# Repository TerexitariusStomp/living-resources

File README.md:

# living-resources

A living sensing commons: cheap, passive, **universal** field nodes relay
multimodal ecological detections over Reticulum to a Playnet edge, where
readings become witnessed receipts and receipts become credit for the
ecology that produced them.

License: AGPL-3.0-or-later.

## The node

One board, every lane's electronics populated (~$35–45 BOM):

camera (OV2640) · air mic (INMP441, 48 kHz/16-bit) · env
(BME280/BH1750/PIR) · hydrophone front-end · ultrasonic MEMS (20–100 kHz)
· C4D contactless front-end · 40 kHz emit transducer · microSD · Reticulum
(WiFi/LoRa/satellite)

A node's role is software + which head is in the environment — never a
different product. See `spec/living-resources.md`.

## The rules that make it a commons

- Every ecological subject is an agent with a human guardian and
  **voice 0** — it earns, it never speaks.
- `sense`/`fleet` lanes admit on **evidence** (a SAID on the lane's gate).
- `emit`/`cast`/`store` admit on **joint guardian+operator consent** —
  bio-write and cloud-write are decisions, not defaults.
- `hop`/`compute`/`engineered` refuse outright — consent is not evidence.
- Every refusal is a structured value; every emission is logged and
  receipted.

## Quickstart

```bash
make test                  # e2e under guile; static checks without it
make check-custom-budget   # the ≤5% first-party rule
```

E0 field validation (see `docs/EXPERIMENTS.md`): flash
`firmware/node/main.py` to a XIAO ESP32-S3 Sense, run the edge adapters
against the node's detection stream, score detections blinded.

## Layout

```
module/living/   specs · agents · sense-subject · attest · settlement · offers
adapters/        mic · camera · reticulum · weather   (thin seams; ML stays
                 Python-side)
firmware/node/   MicroPython universal node (incl. consent-gated EmitLane)
deploy/policies/ OPA: lane-gate.rego · consent.rego
spec/            the system spec
docs/            ARCHITECTURE (component map) · SCIENCE (claim table)
                 · EXPERIMENTS (E-gates) · ROADMAP · CONNECTOME
                 · EFFICIENCY · FUNDING (+ funding/ app drafts)
tests/e2e/       sensing-cell · refused-lanes · write-lanes
tools/edge/      classify.py (edge ML seam) · rns_edge.py (LXMF daemon)
tools/e0/        score.py (blinded field-validation scorer)
tools/e5/        relay_check.py (E5 hop-graduation harness)
```

## Non-interference

Passive by default: nothing attaches to an organism, nothing enters soil,
no anchor moorings, no flash or IR. Emission exists — it is a lane the
commons can ride — and it rides only on recorded joint consent, at
duty-cycled minimum power, with every burst on the ledger.

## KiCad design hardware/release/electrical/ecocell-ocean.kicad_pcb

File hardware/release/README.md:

# EcoCell Ocean — Engineering Release

This directory is the manufacturing package for the ocean-capable EcoCell
node: pressure-rated submerged electronics body plus a minimal-signature
tether float (GPS, antenna, solar). One serialized design covers both the
tether-float and fully submerged-pod forms — the same node electronics,
deployment role chosen by firmware flags.

## Release levels

- **R0 — prototype fab package.** A supplier-reviewable package a fab can
  quote and build from: native KiCad sources, netlist, DSN, Gerbers +
  drill, CPL, controlled BOM, assembly + harness drawings, stack-up/fab
  drawing, test plan, unit traveler, and this README with a checksummed
  manifest. R0 does **not** claim validated pressure rating, ecological
  benefit, or field performance — it claims the design files are
  consistent, DRC-clean, and buildable.
- **R1 — validated build.** R0 plus: assembled units pass TEST-PLAN,
  pressure/leak spec verified on the hull, Salton Sea serialized trial
  complete, DFM/DFT review closed with the supplier.

## Configuration identity

| Item | Value |
|---|---|
| Board | `ecocell-ocean` — 120 × 90 mm, 4-layer (F.Cu / In1 GND / In2 +3V3 / B.Cu) |
| Electrical rev | generated by `tools/pcb/gen_ocean_sch.py` + `gen_ocean_pcb.py` from the same netlist |
| Enclosure revision | `TBD` — pressure-hull + biota-disguised float CAD pending |
| Firmware revision | `firmware/node/main.py` as committed; image hash recorded per unit |
| Regional radio variant | `E22-400M22S` (433 MHz) or `E22-900M22S` (868/915) — one per build, declared |
| Approved suppliers | `TBD` — quote-backed, per-part, with lifecycle/stock check |

## Regenerating the electrical package

```
python3 tools/pcb/gen_ocean_sch.py          # writes electrical/ecocell-ocean.net
python3 tools/pcb/gen_ocean_pcb.py          # placement + DSN export
STITCH=1 python3 tools/pcb/gen_ocean_pcb.py # adds the stitch router (slow)
POST_ONLY=1 python3 tools/pcb/gen_ocean_pcb.py
    # resume: re-run only the post-attach island pass on the saved board
```

Fabrication rules baked into the generator: ≥0.2 mm clearance, ≥0.15 mm
track, 0.5/0.3 mm vias, ≥0.5 mm copper-to-edge, mounting-hole and
ESP32 antenna keepouts.

Known substitutions vs the ideal BOM:

| Ref | Part | Footprint used | Note |
|---|---|---|---|
| U_CHG | TP4056 | `SOIC-8-1EP_3.9x4.9mm_P1.27mm_EP2.41x3.81mm` | ESOP-8 footprint absent from stock KiCad libs; pin-compatible SOIC-8-EP used — verify land pattern against the chosen charger MPN before ordering |

## Release artifacts (required for R0)

| Artifact | Path / source | Status |
|---|---|---|
| Native KiCad schematic | `hardware/release/electrical/ecocell-ocean.net` | **present** — deterministic netlist emitter (SKiDL source lost in workspace wipe; regenerate `.kicad_sch` pending) |
| Native KiCad PCB | `hardware/release/electrical/ecocell-ocean.kicad_pcb` | **present** — placed + autorouted; DRC status tracked below |
| Gerbers + drill (or IPC-2581) | `hardware/release/electrical/` | **missing** — export after DRC is clean |
| Board stack-up / fab drawing | `hardware/release/FAB-NOTES.md` | **present** — stack-up + CAM notes; fiducials flagged as R0 gap |
| Controlled BOM (MPN + alternates) | `hardware/release/electrical/ecocell-ocean-bom.csv` | **present** — generated from the netlist; MPNs/quoting unverified |
| CPL with verified origin/rotation | `hardware/release/assembly/` | **missing** — export post-DRC |
| Assembly drawing | `hardware/release/assembly/` | **missing** |
| Harness drawings | `hardware/release/HARNESS.md` | **present** — connector pinouts + tether spec from the netlist |
| Mechanical CAD + STEP + drawings | `hardware/release/mechanical/` | **missing** — pressure hull, optical port, tether, float |
| Pressure/leak spec | `hardware/release/PRESSURE-SPEC.md` | **present** — 0.4 MPa working / 0.6 MPa proof envelope; hull FEA + O-ring sizing open |
| Test fixture spec | `hardware/release/TEST-PLAN.md` | **present** |
| Unit traveler / calibration record | `hardware/release/UNIT-TRAVELER.md` | **present** |
| Firmware image + hash | `hardware/release/firmware-image.json` | **partial** — source-tree hash recorded; reproducible cross-build pending |
| Release manifest + checksums | `hardware/release/manifest.json` | **present** |
| DFM/DFT review record | `hardware/release/` | **missing** — supplier engagement required |

No artifact may be silently replaced: any change goes through the ECO
procedure below and bumps the relevant revision.

## ECO procedure

1. Describe the change in `CHANGELOG.md` (rev, scope, reason, risk).
2. Regenerate affected artifacts from source — never hand-edit Gerbers,
   CPL, or the manifest.
3. Re-run DRC on the board and the repo checks (`make test`,
   `make check-custom-budget`); record results in the manifest.
4. Re-hash every shipped artifact into `manifest.json` and bump the
   package checksum.
5. A second reviewer signs off before the package is quoted to a fab.

## Honest-status notes

- The board currently validates as *routed*, not *fabrication-ready*:
  DRC must report 0 errors/0 unconnected before Gerbers are exported
  and the "KiCad PCB" row moves to verified.
- Acoustic playback hardware (emit lane) is consent-gated in firmware
  and policy; no ecological effect is claimed from this package.

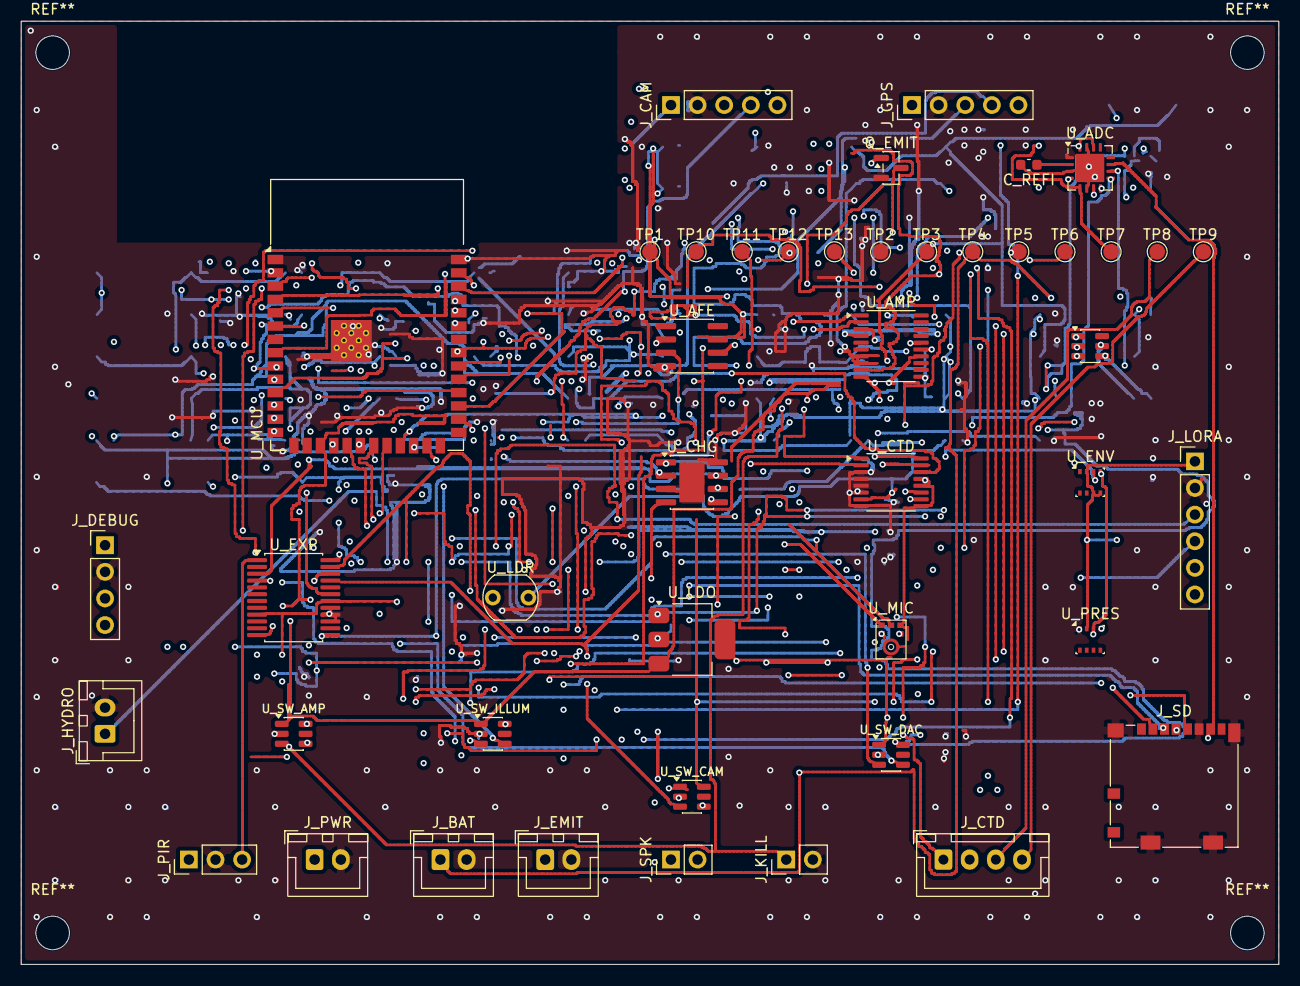
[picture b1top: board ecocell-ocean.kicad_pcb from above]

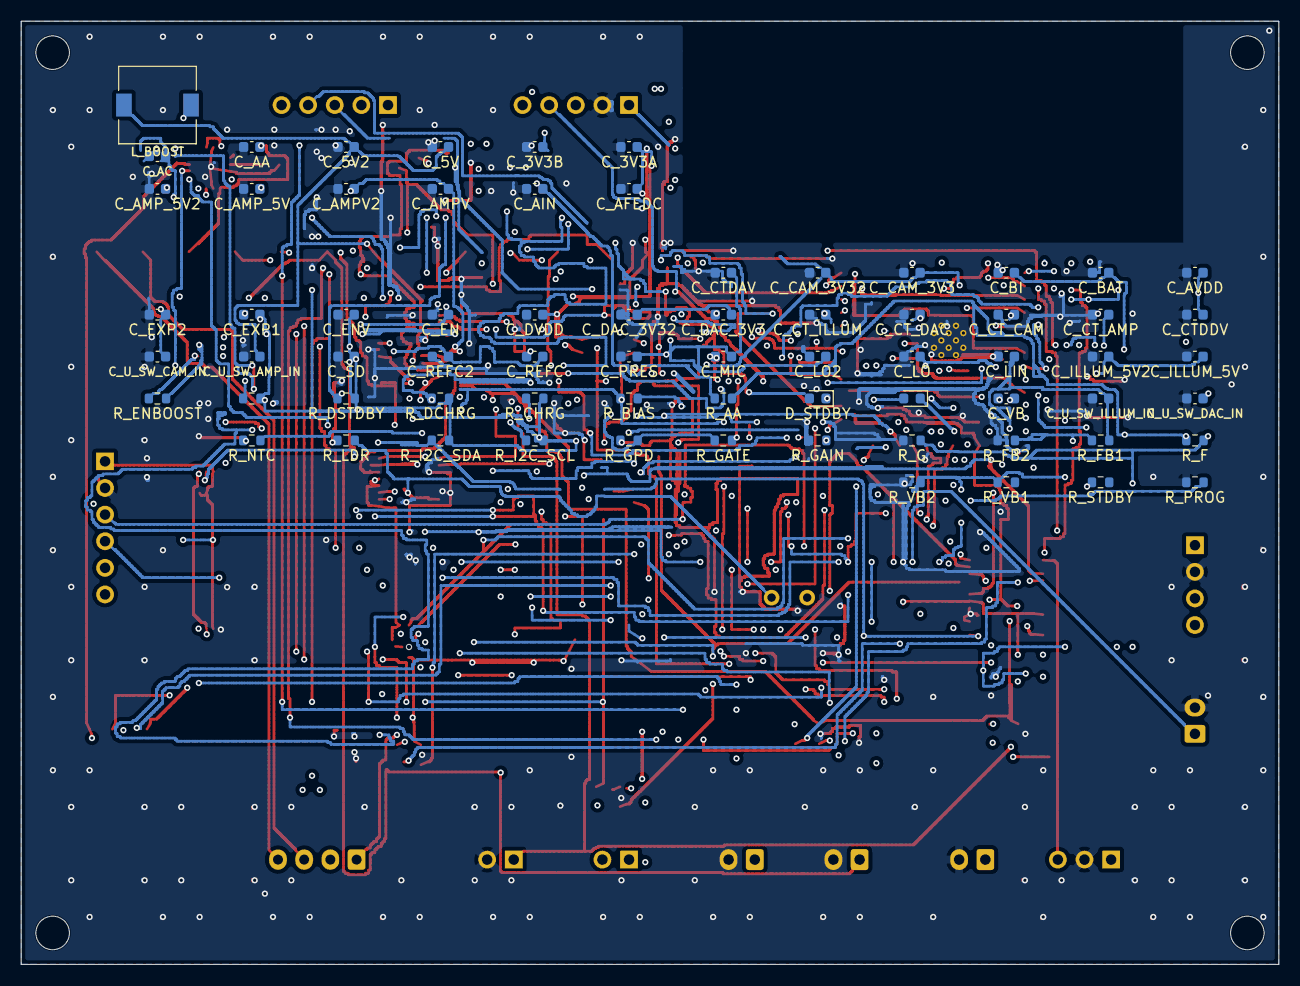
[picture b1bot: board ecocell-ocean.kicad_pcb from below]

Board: 4 copper layers, 120.0 x 90.0 mm, 115 parts (70 on the bottom side), 76 nets.

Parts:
C_3V3A, C_3V3B, C_5V, C_5V2: TPS27081A; C_0603_1608Metric
C_AA: TPS27081A; C_0603_1608Metric
C_AC: TPS27081A; C_0603_1608Metric
C_AFEDC: TPS27081A; C_0603_1608Metric
C_AIN: TPS27081A; C_0603_1608Metric
C_AMPV, C_AMPV2: TPS27081A; C_0603_1608Metric
C_AMP_5V, C_AMP_5V2: TPS27081A; C_0603_1608Metric
C_AVDD: TPS27081A; C_0603_1608Metric
C_BAT: TPS27081A; C_0603_1608Metric
C_BI: TPS27081A; C_0603_1608Metric
C_CAM_3V3, C_CAM_3V32: TPS27081A; C_0603_1608Metric
C_CTDAV: TPS27081A; C_0603_1608Metric
C_CTDDV: TPS27081A; C_0603_1608Metric
C_CT_AMP: TPS27081A; C_0603_1608Metric
C_CT_CAM: TPS27081A; C_0603_1608Metric
C_CT_DAC: TPS27081A; C_0603_1608Metric
C_CT_ILLUM: TPS27081A; C_0603_1608Metric
C_DAC_3V3, C_DAC_3V32: TPS27081A; C_0603_1608Metric
C_DVDD: TPS27081A; C_0603_1608Metric
C_EN: TPS27081A; C_0603_1608Metric
C_ENV: TPS27081A; C_0603_1608Metric
C_EXP1, C_EXP2: TPS27081A; C_0603_1608Metric
C_ILLUM_5V, C_ILLUM_5V2: TPS27081A; C_0603_1608Metric
C_LIN: TPS27081A; C_0603_1608Metric
C_LO, C_LO2: TPS27081A; C_0603_1608Metric
C_MIC: TPS27081A; C_0603_1608Metric
C_PRES: TPS27081A; C_0603_1608Metric
C_REFC, C_REFC2: TPS27081A; C_0603_1608Metric
C_REFI: 100nF; C_0603_1608Metric
C_SD: TPS27081A; C_0603_1608Metric
C_U_SW_AMP_IN: TPS27081A; C_0603_1608Metric
C_U_SW_CAM_IN: TPS27081A; C_0603_1608Metric
C_U_SW_DAC_IN: TPS27081A; C_0603_1608Metric
C_U_SW_ILLUM_IN: TPS27081A; C_0603_1608Metric
C_VB: TPS27081A; C_0603_1608Metric
D_CHRG: TPS27081A; LED_0603_1608Metric
D_STDBY: TPS27081A; LED_0603_1608Metric
J_BAT: BAT; JST_XH_B2B-XH-A_1x02_P2.50mm_Vertical
J_CAM: CAM; PinHeader_1x05_P2.54mm_Vertical
J_CTD: CTD; JST_XH_B4B-XH-A_1x04_P2.50mm_Vertical
J_DEBUG: DEBUG; PinHeader_1x04_P2.54mm_Vertical
J_EMIT: EMIT; JST_XH_B2B-XH-A_1x02_P2.50mm_Vertical
J_GPS: GPS; PinHeader_1x05_P2.54mm_Vertical
J_HYDRO: HYDRO; JST_XH_B2B-XH-A_1x02_P2.50mm_Vertical
J_KILL: KILL; PinHeader_1x02_P2.54mm_Vertical
J_LORA: LORA; PinHeader_1x06_P2.54mm_Vertical
J_PIR: PIR; PinHeader_1x03_P2.54mm_Vertical
J_PWR: PWR; JST_XH_B2B-XH-A_1x02_P2.50mm_Vertical
J_SD: microSD; microSD_HC_Molex_104031-0811
J_SPK: SPK; PinHeader_1x02_P2.54mm_Vertical
L_BOOST: TPS27081A; L_7.3x7.3_H4.5
Q_EMIT: 2N7002; SOT-23
R_AA: TPS27081A; R_0603_1608Metric
R_BIAS: TPS27081A; R_0603_1608Metric
R_CHRG: TPS27081A; R_0603_1608Metric
R_DCHRG: TPS27081A; R_0603_1608Metric
R_DSTDBY: TPS27081A; R_0603_1608Metric
R_EN: TPS27081A; R_0603_1608Metric
R_ENBOOST: TPS27081A; R_0603_1608Metric
R_F: TPS27081A; R_0603_1608Metric
R_FB1, R_FB2: TPS27081A; R_0603_1608Metric
R_G: TPS27081A; R_0603_1608Metric
R_GAIN: TPS27081A; R_0603_1608Metric
R_GATE: TPS27081A; R_0603_1608Metric
R_GPD: TPS27081A; R_0603_1608Metric
R_I2C_SCL, R_I2C_SDA: TPS27081A; R_0603_1608Metric
R_LDR: TPS27081A; R_0603_1608Metric
R_NTC: TPS27081A; R_0603_1608Metric
R_PROG: TPS27081A; R_0603_1608Metric
R_STDBY: TPS27081A; R_0603_1608Metric
R_VB1, R_VB2: TPS27081A; R_0603_1608Metric
TP1, TP2, TP3, TP4, TP5, TP6, TP7, TP8, TP9, TP10, TP11, TP12, TP13: TP; TestPoint_Pad_D1.5mm
U_ADC: ADS8681; QFN-16-1EP_4x4mm_P0.65mm_EP2.7x2.7mm
U_AFE: OPA333; SOIC-8_3.9x4.9mm_P1.27mm
U_AMP: PCM5102A; TSSOP-20_4.4x6.5mm_P0.65mm
U_BOOST: MT3608; SOT-23-6
U_CHG: TP4056; SOIC-8-1EP_3.9x4.9mm_P1.27mm_EP2.41x3.81mm
U_CTD: ADS1220; TSSOP-16_4.4x5mm_P0.65mm
U_ENV: BME280; Bosch_LGA-8_2.5x2.5mm_P0.65mm_ClockwisePinNumbering
U_EXP: TCA9535DBT; SSOP-24_5.3x8.2mm_P0.65mm
U_LDO: AMS1117-3.3; SOT-223-3_TabPin2
U_LDR: GL5528; R_LDR_5.1x4.3mm_P3.4mm_Vertical
U_MCU: ESP32-S3-WROOM-1
U_MIC: ICS-43434; InvenSense_ICS-43434-6_3.5x2.65mm
U_PRES: BMP390; Bosch_LGA-8_2.5x2.5mm_P0.65mm_ClockwisePinNumbering
U_SW_AMP: TPS27081A; SOT-23-6
U_SW_CAM: TPS27081A; SOT-23-6
U_SW_DAC: TPS27081A; SOT-23-6
U_SW_ILLUM: TPS27081A; SOT-23-6

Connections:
+3V3: C_3V3A.1, C_3V3B.1, C_AFEDC.1, C_AVDD.1, C_CTDAV.1, C_CTDDV.1, C_DVDD.1, C_ENV.1, C_EXP1.1, C_EXP2.1, C_LO.1, C_LO2.1, C_MIC.1, C_PRES.1, C_SD.1, C_U_SW_CAM_IN.1, C_U_SW_DAC_IN.1, J_DEBUG.1, J_GPS.1, J_LORA.1, J_PIR.1, J_SD.4, R_CHRG.1, R_DCHRG.1, R_DSTDBY.1, R_EN.1, R_I2C_SCL.1, R_I2C_SDA.1, TP1.1, U_ADC.14, U_ADC.16, U_AFE.7, U_AMP.4, U_CTD.9, U_CTD.12, U_CTD.13, U_ENV.2, U_ENV.5, U_ENV.6, U_EXP.9, U_EXP.18, U_LDO.2, U_LDR.1, U_MCU.2, U_MIC.5, U_PRES.2, U_SW_CAM.1, U_SW_DAC.1
+5V: C_5V.1, C_5V2.1, C_LIN.1, C_U_SW_AMP_IN.1, C_U_SW_ILLUM_IN.1, L_BOOST.2, R_FB1.1, TP3.1, U_LDO.3, U_SW_AMP.1, U_SW_ILLUM.1
ADC_AIN: C_AA.1, C_AIN.1, R_AA.2, TP7.1, U_ADC.5
ADC_RST: U_ADC.7, U_MCU.8
ADS_CS: U_CTD.2, U_MCU.25
ADS_DIN: U_CTD.16, U_MCU.23
ADS_DOUT: U_CTD.15, U_MCU.24
ADS_DRDY: U_CTD.14, U_MCU.28
ADS_SCK: U_CTD.1, U_MCU.11
AFE_INP: C_AC.2, R_BIAS.2, U_AFE.3
AFE_N: R_F.1, R_G.1, U_AFE.2
AFE_OUT: R_AA.1, R_F.2, TP6.1, U_AFE.6
AMP_5V: C_AMPV.1, C_AMPV2.1, C_AMP_5V.1, C_AMP_5V2.1, U_AMP.7, U_AMP.8, U_SW_AMP.6
CAM_3V3: C_CAM_3V3.1, C_CAM_3V32.1, J_CAM.1, U_SW_CAM.6
CHRG_ST: D_CHRG.1, R_CHRG.2, U_CHG.7, U_EXP.3
CTD_EXC_N: J_CTD.4, TP9.1
CTD_EXC_P: J_CTD.3, TP8.1
CTD_S_N: J_CTD.2, U_CTD.10
CTD_S_P: J_CTD.1, U_CTD.11
CT_AMP: C_CT_AMP.1, U_SW_AMP.4
CT_CAM: C_CT_CAM.1, U_SW_CAM.4
CT_DAC: C_CT_DAC.1, U_SW_DAC.4
CT_ILLUM: C_CT_ILLUM.1, U_SW_ILLUM.4
DAC_3V3: C_DAC_3V3.1, C_DAC_3V32.1, U_SW_DAC.6
DEBUG_RX: J_DEBUG.4, U_MCU.36
DEBUG_TX: J_DEBUG.3, U_MCU.37
EMIT_GATE: Q_EMIT.1, R_GATE.2, R_GPD.1
EMIT_PWM: R_GATE.1, U_MCU.39
EMIT_SIG: J_EMIT.1, Q_EMIT.3
EN: C_EN.1, R_EN.2, U_MCU.3
EN_AMP: J_KILL.1, TP11.1, U_EXP.22, U_SW_AMP.3
EN_BOOST: R_ENBOOST.2, U_BOOST.4
EN_CAM: TP10.1, U_EXP.21, U_SW_CAM.3
EN_ILLUM: TP12.1, U_EXP.23, U_SW_ILLUM.3
EN_PLAY: TP13.1, U_EXP.24, U_SW_DAC.3
EXP_INT: U_EXP.19, U_MCU.14
FB: R_FB1.2, R_FB2.1, U_BOOST.3
GAIN_SLOT: R_GAIN.1, U_AMP.2
GND: C_3V3A.2, C_3V3B.2, C_5V.2, C_5V2.2, C_AA.2, C_AFEDC.2, C_AIN.2, C_AMPV.2, C_AMPV2.2, C_AMP_5V.2, C_AMP_5V2.2, C_AVDD.2, C_BAT.2, C_BI.2, C_CAM_3V3.2, C_CAM_3V32.2, C_CTDAV.2, C_CTDDV.2, C_CT_AMP.2, C_CT_CAM.2, C_CT_DAC.2, C_CT_ILLUM.2, C_DAC_3V3.2, C_DAC_3V32.2, C_DVDD.2, C_EN.2, C_ENV.2, C_EXP1.2, C_EXP2.2, C_ILLUM_5V.2, C_ILLUM_5V2.2, C_LIN.2, C_LO.2, C_LO2.2, C_MIC.2, C_PRES.2, C_REFC.2, C_REFC2.2, C_REFI.2, C_SD.2, C_U_SW_AMP_IN.2, C_U_SW_CAM_IN.2, C_U_SW_DAC_IN.2, C_U_SW_ILLUM_IN.2, C_VB.2, J_BAT.2, J_CAM.2, J_DEBUG.2, J_EMIT.2, J_GPS.2, J_HYDRO.2, J_KILL.2, J_LORA.2, J_PIR.2, J_PWR.2, J_SD.6, J_SD.SH, Q_EMIT.2, R_FB2.2, R_G.2, R_GAIN.2, R_GPD.2, R_LDR.2, R_NTC.2, R_PROG.2, R_VB2.2, TP2.1, U_ADC.1, U_ADC.3, U_ADC.6, U_ADC.15, U_ADC.17, U_AFE.4, U_AMP.3, U_AMP.11, U_AMP.15, U_BOOST.2, U_CHG.3, U_CHG.8, U_CHG.9, U_CTD.3, U_CTD.4, U_CTD.5, U_CTD.6, U_CTD.8, U_EXP.15, U_EXP.16, U_EXP.17, U_LDO.1, U_MCU.1, U_MCU.40, U_MCU.41, U_MIC.2, U_MIC.3, U_PRES.1, U_SW_AMP.2, U_SW_CAM.2, U_SW_DAC.2, U_SW_ILLUM.2
HYDRO_SIG: C_AC.1, J_HYDRO.1
I2C_SCL: R_I2C_SCL.2, U_ENV.4, U_EXP.12, U_MCU.17, U_PRES.3
I2C_SDA: R_I2C_SDA.2, U_ENV.3, U_EXP.13, U_MCU.12, U_PRES.4
I2S0_BCLK: U_MCU.18, U_MIC.4
I2S0_SD: U_MCU.13, U_MIC.6
I2S0_WS: U_MCU.10, U_MIC.1
I2S1_BCLK: U_AMP.16, U_MCU.4
I2S1_DIN: U_AMP.1, U_MCU.6
I2S1_LRCK: U_AMP.14, U_MCU.5
ILLUM_5V: C_ILLUM_5V.1, C_ILLUM_5V2.1, U_SW_ILLUM.6
LDR_OUT: R_LDR.1, U_CTD.7, U_LDR.2
LED_CHRG_A: D_CHRG.2, R_DCHRG.2
LED_STDBY_A: D_STDBY.2, R_DSTDBY.2
NTC: R_NTC.1, U_CHG.1
PIR_OUT: J_PIR.3, U_EXP.1
PPS: J_GPS.5, U_MCU.29
PROG: R_PROG.1, U_CHG.2
REFCAP: C_REFC.1, C_REFC2.1, U_ADC.4
REFIO: C_REFI.1, U_ADC.2
SD_CS: J_SD.2, U_MCU.38
SPI2_CS: U_ADC.9, U_MCU.22
SPI2_MISO: J_SD.7, U_ADC.11, U_MCU.21
SPI2_MOSI: J_SD.3, U_ADC.8, U_MCU.19
SPI2_SCK: J_SD.5, U_ADC.10, U_MCU.20
SPK_N: J_SPK.2, U_AMP.10
SPK_P: J_SPK.1, U_AMP.9
STDBY_ST: D_STDBY.1, R_STDBY.2, U_CHG.6, U_EXP.4
SW: L_BOOST.1, U_BOOST.1
UART1_RX: J_LORA.3, U_MCU.30
UART1_TX: J_LORA.4, U_MCU.33
UART2_RX: J_GPS.3, U_MCU.31
UART2_TX: J_GPS.4, U_MCU.35
UART3_RX: J_CAM.3, U_MCU.32
UART3_TX: J_CAM.4, U_MCU.9
VBAT: C_BAT.1, C_BI.1, J_BAT.1, R_ENBOOST.1, TP4.1, U_BOOST.5, U_CHG.5
VBIAS: C_VB.1, R_BIAS.1, R_VB1.2, R_VB2.1, TP5.1
VIN: J_PWR.1, U_CHG.4

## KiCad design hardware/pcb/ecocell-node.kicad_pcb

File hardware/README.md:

# hardware/ — EcoCell universal node

One board design. Every lane's electronics on every unit. Role =
firmware config + which head sits in the environment — never a variant,
never an upgrade purchase.

## What to read in what order

| File | For |
|---|---|
| `BOM.md` | What to buy — core board + every head + per-deployment kits |
| `FIELD-KIT.md` | **Complete sourcing matrix** — Seeed-assembled vs plug-in vs field kit, first-article test plan |
| `PROVISIONING.md` | **Parcel→live node** — flash, identity, consent defaults, edge pairing, commissioning |
| `PINOUT.md` | How it wires — the pin map the firmware and heads share |
| `ASSEMBLY.md` | How to build — solder points, flash steps, bench test |
| `ENCLOSURE.md` | How to deploy — garden / shore-dock / reef-float / submerged forms |
| `DATASHEET.md` | The tender-attachable product sheet (prospective — v1 target) |
| `PCB.md` | **Manufacturable carrier** — KiCad source, DRC-clean Gerbers, Seeed ordering |
| `diagrams/wiring.svg` | **Visual: full wiring diagram** — every pin→head wire, net colors |
| `diagrams/layout.svg` | **Visual: carrier top-view** — component placement on perfboard |
| `diagrams/enclosure-forms.svg` | **Visual: 4 cross-sections** — garden/shore/float/pod |

## The build in one picture

```
        ┌──────────────────── XIAO ESP32-S3 Sense ───────────────────┐
        │  onboard: OV2640 camera · PDM mic · microSD · ESP32-S3     │
        │                                                           │
  D0 PIR wake ──┐            ┌── D4/D5  I2C bus ──────────────────┐  │
  D1 hydro ADC  │            │  BME280 · BH1750 · AD7746 (C4D)    │  │
  D2 ultra ADC  │            └────────────────────────────────────┘  │
  D3 emit PWM ──┼──▶ 40 kHz transducer driver (consent-gated)        │
  D6/D7 UART ───┼──▶ LoRa RNode / satellite modem / serial gateway   │
  D8–D10 SPI ───┴──▶ spare (expansion: second SD, display, GPS)      │
        └───────────────────────────────────────────────────────────┘
```

## Two build paths

1. **Hand build (v1, now):** XIAO ESP32-S3 Sense + breakout modules on
   headers — no PCB fab needed, ~1–2 h per unit, ~$35–45.
2. **Carrier board (v2, tender path):** `pcb/` holds a **DRC-clean,
   fab-ready KiCad design** — upload `gerbers/ecocell-carrier-gerbers.zip`
   to Seeed Fusion (2-layer, 100×80, standard spec). v2 adds the field
   layer: screw-terminal 5V input, fuse, reverse-polarity Schottky, rail
   TVS, ESD clamps on the head inputs, power LED, fiducials. See `PCB.md`
   for the package and `FIELD-KIT.md` for everything else a deployable
   node still needs (XIAO, heads, radio, power, enclosure).

## Honest flags

- Pin assignments in `PINOUT.md` are the recommended map — **verify the
  free-GPIO set against your board revision's schematic** (XIAO Sense
  expansion board occupies internal pins for camera/mic/SD).
- The ultrasonic lane's 20–100 kHz band exceeds what the ESP32 ADC path
  samples comfortably — the head and wiring are ready; firmware capture
  may need decimation tricks or the C++ firmware variant. Noted in
  `PINOUT.md`, not hidden.
- Emit lane: hardware is live on every board; activation is purely a
  consent flag — see `deploy/policies/living/` and `firmware/node/main.py`.

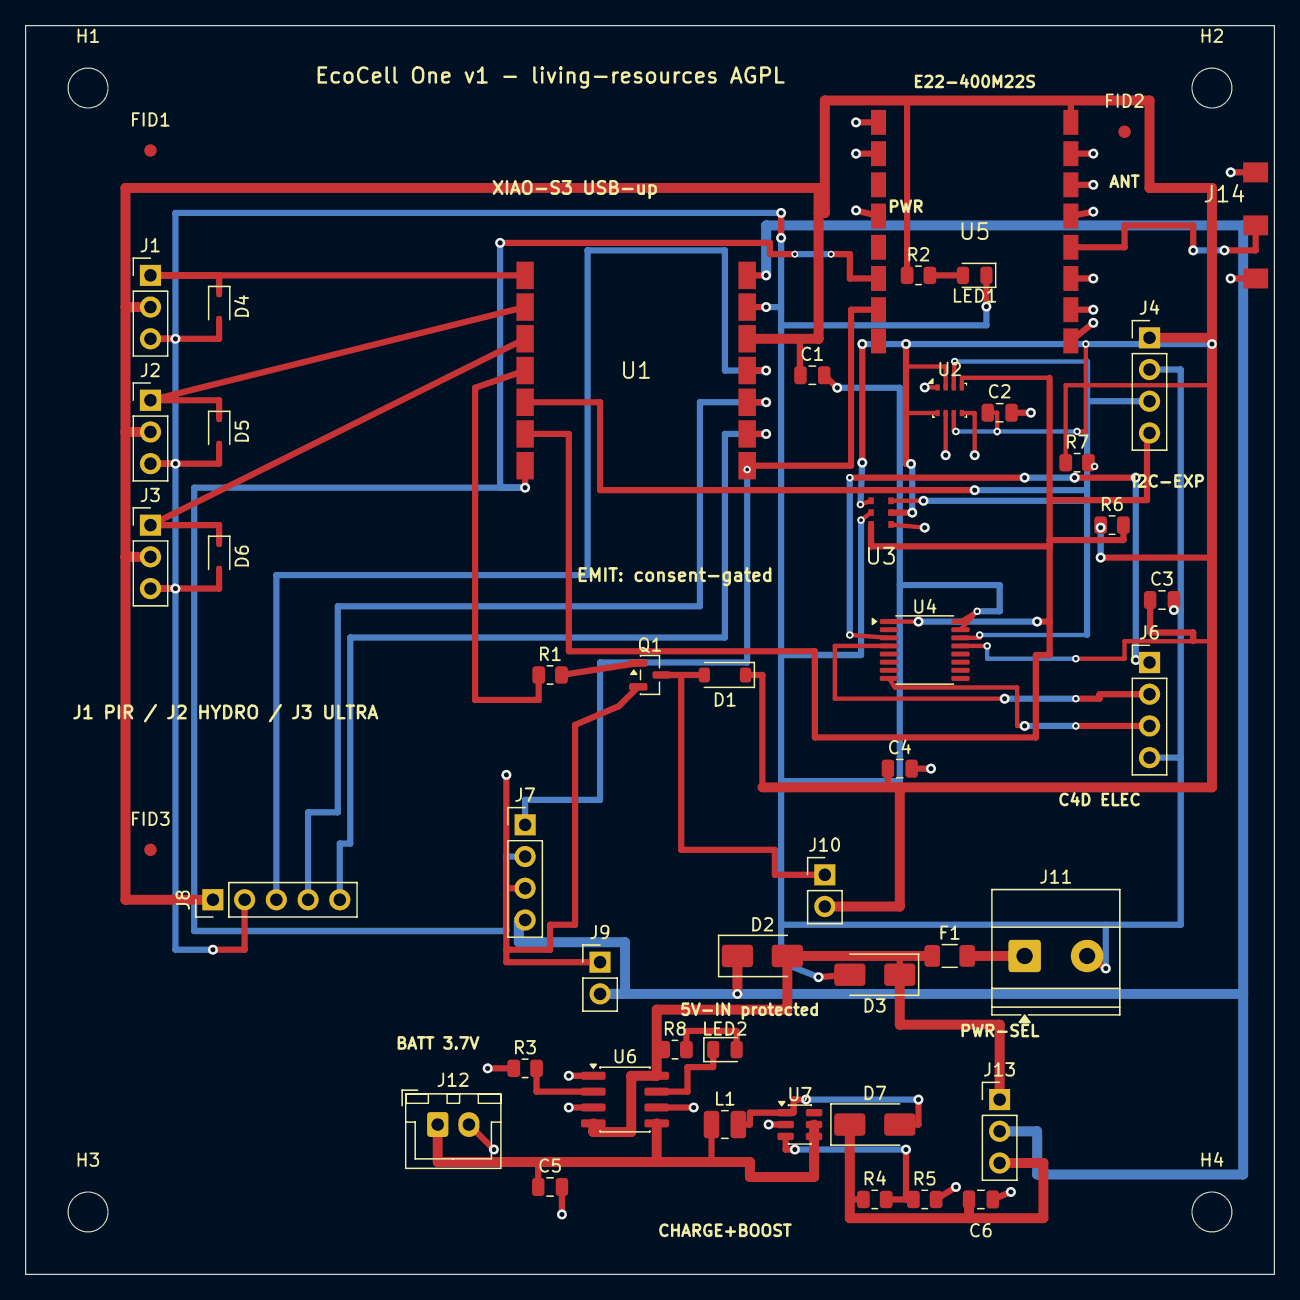
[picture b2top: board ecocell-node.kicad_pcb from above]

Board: 2 copper layers, 100.0 x 100.0 mm, 53 parts (0 on the bottom side), 30 nets.

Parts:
C1, C2, C3, C4: 100nF; C_0805_2012Metric
C5, C6: 22uF; C_0805_2012Metric
D1: 1N4148W; D_SOD-123
D2, D7: SS14; D_SMA
D3: SMAJ5.0A; D_SMA
D4, D5, D6: PESD5V0; D_SOD-323
F1: 0.75A; Fuse_1206_3216Metric
FID1, FID2, FID3: FID; Fiducial_1mm_Mask3mm
H1, H2, H3, H4: M3; MountingHole_3.2mm_M3
J1: PIR; PinHeader_1x03_P2.54mm_Vertical
J2: HYDRO; PinHeader_1x03_P2.54mm_Vertical
J3: ULTRA; PinHeader_1x03_P2.54mm_Vertical
J4: I2C-EXP; PinHeader_1x04_P2.54mm_Vertical
J6: C4D-ELEC; PinHeader_1x04_P2.54mm_Vertical
J7: UART; PinHeader_1x04_P2.54mm_Vertical
J8: SPI; PinHeader_1x05_P2.54mm_Vertical
J9: 5V-IN; PinHeader_1x02_P2.54mm_Vertical
J10: EMIT-40k; PinHeader_1x02_P2.54mm_Vertical
J11: 5V-SCREW; TerminalBlock_Phoenix_MKDS-1,5-2_1x02_P5.00mm_Horizontal
J12: BATT-3.7V; JST_XH_B2B-XH-A_1x02_P2.50mm_Vertical
J13: PWR-SEL; PinHeader_1x03_P2.54mm_Vertical
J14: SMA-EDGE
L1: 22uH; L_1008_2520Metric
LED1: PWR-GRN; LED_0805_2012Metric
LED2: CHRG-RED; LED_0805_2012Metric
Q1: 2N7002; SOT-23
R1: 100R; R_0805_2012Metric
R2, R8: 1k; R_0805_2012Metric
R3: 1.2k; R_0805_2012Metric
R4: 75k; R_0805_2012Metric
R5: 10k; R_0805_2012Metric
R6, R7: 4.7k; R_0805_2012Metric
U1: XIAO-ESP32S3
U2: BME280; Bosch_LGA-8_2.5x2.5mm_P0.65mm_ClockwisePinNumbering
U3: BH1750
U4: AD7746; TSSOP-16_4.4x5mm_P0.65mm
U5: E22-400M22S
U6: TP4056; SOP-8_3.76x4.96mm_P1.27mm
U7: MT3608; SOT-23-6

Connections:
+3V3: C1.1, C2.1, C3.1, C4.1, D1.1, J1.2, J2.2, J3.2, J4.1, J8.1, J10.2, R2.1, R6.1, R7.1, U1.10, U2.2, U2.6, U2.8, U3.1, U3.5, U4.13, U5.9
+5V: D2.1, J7.4, J9.2, J13.2, U1.8
ANT: J14.1, U5.13
CHRG_LED: LED2.2, R8.2
CHRG_N: LED2.1, U6.7
CIN_P: J6.3, U4.8
D0_PIR: D4.1, J1.1, U1.1
D1_HYDRO: D5.1, J2.1, U1.2
D2_ULTRA: D6.1, J3.1, U1.3
D3_EMIT: R1.1, U1.4
EMIT_GATE: Q1.1, R1.2
EMIT_SW: D1.2, J10.1, Q1.3
EXC_A: J6.1, U4.3
EXC_B: J6.2, U4.4
FB_NODE: R4.2, R5.1, U7.3
GND: C1.2, C2.2, C3.2, C4.2, C5.2, C6.2, D3.2, D4.2, D5.2, D6.2, J1.3, J2.3, J3.3, J4.2, J6.4, J7.3, J8.2, J9.1, J11.2, J12.2, J14.2, LED1.1, Q1.2, R3.1, R5.2, U1.9, U2.1, U2.5, U2.7, U3.2, U3.4, U4.15, U4.16, U5.1, U5.2, U5.4, U5.10, U5.11, U5.12, U5.14, U5.15, U5.16, U6.1, U6.3, U6.6, U7.2
LEDPWR: LED1.2, R2.2
MISO_D9: J8.4, U1.12
MOSI_D10: J8.3, U1.11
PROG_N: R3.2, U6.2
RX_D7: J7.1, U1.14, U5.7
SCK_D8: J8.5, U1.13
SCL: J4.4, R6.2, U1.6, U2.4, U3.3, U4.1
SDA: J4.3, R7.2, U1.5, U2.3, U3.6, U4.14
SW_NODE: D7.2, L1.2, U7.1
TX_D6: J7.2, U1.7, U5.6
VBATT: C5.1, J12.1, L1.1, U6.5, U7.4, U7.5
VBOOST: C6.1, D7.1, J13.3, R4.1
VIN: F1.2, J11.1
VPROT: D2.2, D3.1, F1.1, J13.1, R8.1, U6.4, U6.8

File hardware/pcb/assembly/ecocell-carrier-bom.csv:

Designator,Val,Package,Layer,Notes
C1,100nF,C_0805_2012Metric,top,SMT - PCBA
D1,1N4148W,D_SOD-123,top,SMT - PCBA
D2,SS14,D_SMA,top,SMT - PCBA
D3,SMAJ5.0A,D_SMA,top,SMT - PCBA
D4,PESD5V0,D_SOD-323,top,SMT - PCBA
D5,PESD5V0,D_SOD-323,top,SMT - PCBA
D6,PESD5V0,D_SOD-323,top,SMT - PCBA
F1,0.75A,Fuse_1206_3216Metric,top,SMT - PCBA
J1,PIR,PinHeader_1x03_P2.54mm_Vertical,top,THT - hand solder
J2,HYDRO,PinHeader_1x03_P2.54mm_Vertical,top,THT - hand solder
J3,ULTRA,PinHeader_1x03_P2.54mm_Vertical,top,THT - hand solder
J4,I2C-BME280,PinHeader_1x04_P2.54mm_Vertical,top,THT - hand solder
J5,I2C-BH1750,PinHeader_1x04_P2.54mm_Vertical,top,THT - hand solder
J6,I2C-AD7746,PinHeader_1x04_P2.54mm_Vertical,top,THT - hand solder
J7,UART,PinHeader_1x04_P2.54mm_Vertical,top,THT - hand solder
J8,SPI,PinHeader_1x05_P2.54mm_Vertical,top,THT - hand solder
J9,5V-IN,PinHeader_1x02_P2.54mm_Vertical,top,THT - hand solder
J10,EMIT-40k,PinHeader_1x02_P2.54mm_Vertical,top,THT - hand solder
J11,5V-SCREW,"TerminalBlock_Phoenix_MKDS-1,5-2_1x02_P5.00mm_Horizontal",top,THT - hand solder
LED1,PWR-GRN,LED_0805_2012Metric,top,SMT - PCBA
Q1,2N7002,SOT-23,top,SMT - PCBA
R1,100R,R_0805_2012Metric,top,SMT - PCBA
R2,1k,R_0805_2012Metric,top,SMT - PCBA
U1A,XIAO-L,PinSocket_1x07_P2.54mm_Vertical,top,THT - hand solder
U1B,XIAO-R,PinSocket_1x07_P2.54mm_Vertical,top,THT - hand solder

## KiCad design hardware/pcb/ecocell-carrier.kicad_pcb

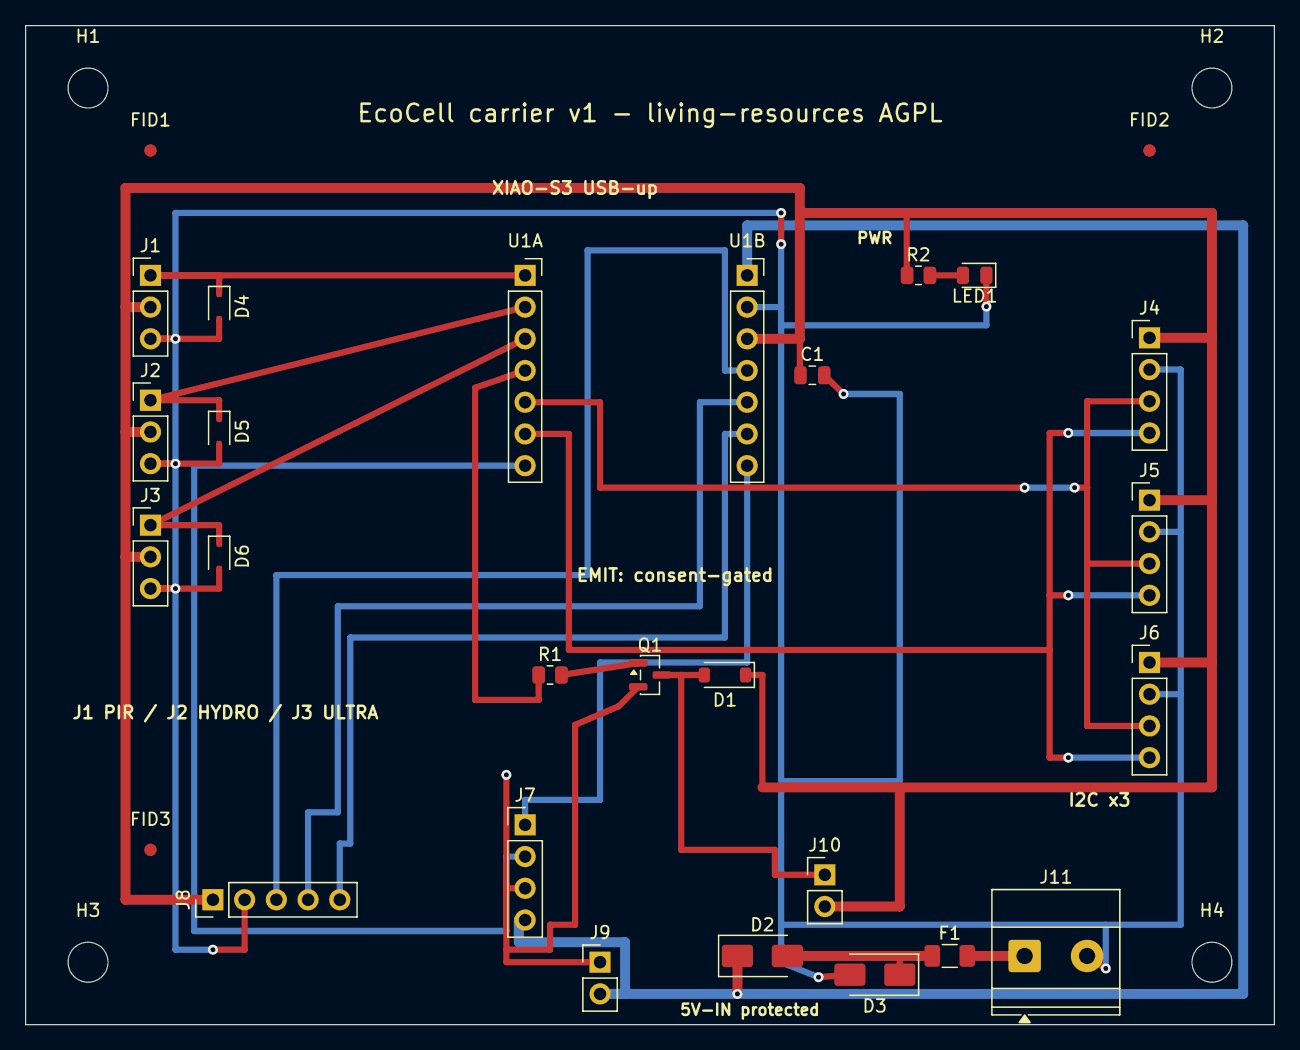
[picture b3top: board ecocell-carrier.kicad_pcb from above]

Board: 2 copper layers, 100.0 x 80.0 mm, 32 parts (0 on the bottom side), 19 nets.

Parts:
C1: 100nF; C_0805_2012Metric
D1: 1N4148W; D_SOD-123
D2: SS14; D_SMA
D3: SMAJ5.0A; D_SMA
D4, D5, D6: PESD5V0; D_SOD-323
F1: 0.75A; Fuse_1206_3216Metric
FID1, FID2, FID3: FID; Fiducial_1mm_Mask3mm
H1, H2, H3, H4: M3; MountingHole_3.2mm_M3
J1: PIR; PinHeader_1x03_P2.54mm_Vertical
J2: HYDRO; PinHeader_1x03_P2.54mm_Vertical
J3: ULTRA; PinHeader_1x03_P2.54mm_Vertical
J4: I2C-BME280; PinHeader_1x04_P2.54mm_Vertical
J5: I2C-BH1750; PinHeader_1x04_P2.54mm_Vertical
J6: I2C-AD7746; PinHeader_1x04_P2.54mm_Vertical
J7: UART; PinHeader_1x04_P2.54mm_Vertical
J8: SPI; PinHeader_1x05_P2.54mm_Vertical
J9: 5V-IN; PinHeader_1x02_P2.54mm_Vertical
J10: EMIT-40k; PinHeader_1x02_P2.54mm_Vertical
J11: 5V-SCREW; TerminalBlock_Phoenix_MKDS-1,5-2_1x02_P5.00mm_Horizontal
LED1: PWR-GRN; LED_0805_2012Metric
Q1: 2N7002; SOT-23
R1: 100R; R_0805_2012Metric
R2: 1k; R_0805_2012Metric
U1A: XIAO-L; PinSocket_1x07_P2.54mm_Vertical
U1B: XIAO-R; PinSocket_1x07_P2.54mm_Vertical

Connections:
+3V3: C1.1, D1.1, J1.2, J2.2, J3.2, J4.1, J5.1, J6.1, J8.1, J10.2, R2.1, U1B.3
+5V: D2.1, J7.4, J9.2, U1B.1
D0_PIR: D4.1, J1.1, U1A.1
D1_HYDRO: D5.1, J2.1, U1A.2
D2_ULTRA: D6.1, J3.1, U1A.3
D3_EMIT: R1.1, U1A.4
EMIT_GATE: Q1.1, R1.2
EMIT_SW: D1.2, J10.1, Q1.3
GND: C1.2, D3.2, D4.2, D5.2, D6.2, J1.3, J2.3, J3.3, J4.2, J5.2, J6.2, J7.3, J8.2, J9.1, J11.2, LED1.1, Q1.2, U1B.2
LEDPWR: LED1.2, R2.2
MISO_D9: J8.4, U1B.5
MOSI_D10: J8.3, U1B.4
RX_D7: J7.1, U1B.7
SCK_D8: J8.5, U1B.6
SCL: J4.4, J5.4, J6.4, U1A.6
SDA: J4.3, J5.3, J6.3, U1A.5
TX_D6: J7.2, U1A.7
VIN: F1.2, J11.1
VPROT: D2.2, D3.1, F1.1

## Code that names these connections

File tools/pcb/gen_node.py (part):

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
# left-edge sensor headers (pin order top->bottom: SIG, 3V3, GND)
place(HDR, "PinHeader_1x03_P2.54mm_Vertical", "J1", "PIR", (10, 20),
      pin_nets={"1": "D0_PIR", "2": "+3V3", "3": "GND"})
place(HDR, "PinHeader_1x03_P2.54mm_Vertical", "J2", "HYDRO", (10, 30),
      pin_nets={"1": "D1_HYDRO", "2": "+3V3", "3": "GND"})
place(HDR, "PinHeader_1x03_P2.54mm_Vertical", "J3", "ULTRA", (10, 40),
      pin_nets={"1": "D2_ULTRA", "2": "+3V3", "3": "GND"})

# right-edge connectors: J4 stays a spare I2C expansion header; the
# BME280/BH1750/AD7746 are now bare ICs on-board, so old J5/J6 slots
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place(HDR, "PinHeader_1x04_P2.54mm_Vertical", "J4", "I2C-EXP", (90, 25),
      pin_nets={"1": "+3V3", "2": "GND", "3": "SDA", "4": "SCL"})
place(HDR, "PinHeader_1x04_P2.54mm_Vertical", "J6", "C4D-ELEC", (90, 51),
      pin_nets={"1": "EXC_A", "2": "EXC_B", "3": "CIN_P", "4": "GND"})

# --- on-board I2C sensor ICs
place("Package_LGA.pretty",
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                "5": "GND", "6": "+3V3", "7": "GND", "8": "+3V3"})
place("Package_SO.pretty", "TSSOP-16_4.4x5mm_P0.65mm", "U4", "AD7746",
      (72, 50),
      pin_nets={"1": "SCL", "3": "EXC_A", "4": "EXC_B", "8": "CIN_P",
                "13": "+3V3", "14": "SDA", "15": "GND", "16": "GND"})
place("Resistor_SMD.pretty", "R_0805_2012Metric", "R6", "4.7k", (87, 40),
      pin_nets={"1": "+3V3", "2": "SCL"})
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# PWR-SEL jumper (BATT vs DIRECT feed of the protected rail)
place("Package_SO.pretty", "SOP-8_3.76x4.96mm_P1.27mm", "U6", "TP4056",
      (48, 86),
      pin_nets={"1": "GND", "2": "PROG_N", "3": "GND", "4": "VPROT",
                "5": "VBATT", "6": "GND", "7": "CHRG_N", "8": "VPROT"})
place("Connector_JST.pretty", "JST_XH_B2B-XH-A_1x02_P2.50mm_Vertical",
      "J12", "BATT-3.7V", (33, 88), pin_nets={"1": "VBATT", "2": "GND"})
place("Package_TO_SOT_SMD.pretty", "SOT-23-6", "U7", "MT3608", (62, 88),
      pin_nets={"1": "SW_NODE", "2": "GND", "3": "FB_NODE",
                "4": "VBATT", "5": "VBATT"})
place("Inductor_SMD.pretty", "L_1008_2520Metric", "L1", "22uH", (56, 88),
      pin_nets={"1": "VBATT", "2": "SW_NODE"})
place("Diode_SMD.pretty", "D_SMA", "D7", "SS14", (68, 88), rot=0,
      pin_nets={"1": "VBOOST", "2": "SW_NODE"})
place("Capacitor_SMD.pretty", "C_0805_2012Metric", "C5", "22uF", (42, 93),
      pin_nets={"1": "VBATT", "2": "GND"})
place("Capacitor_SMD.pretty", "C_0805_2012Metric", "C6", "22uF", (76.5, 94),
      pin_nets={"1": "VBOOST", "2": "GND"})
place("Resistor_SMD.pretty", "R_0805_2012Metric", "R3", "1.2k", (40, 83.5),
      pin_nets={"1": "GND", "2": "PROG_N"})
place("Resistor_SMD.pretty", "R_0805_2012Metric", "R4", "75k", (68, 94),
      pin_nets={"1": "VBOOST", "2": "FB_NODE"})
place("Resistor_SMD.pretty", "R_0805_2012Metric", "R5", "10k", (72, 94),
      pin_nets={"1": "FB_NODE", "2": "GND"})
place("Resistor_SMD.pretty", "R_0805_2012Metric", "R8", "1k", (52, 82),
      pin_nets={"1": "VPROT", "2": "CHRG_LED"})
place("LED_SMD.pretty", "LED_0805_2012Metric", "LED2", "CHRG-RED",
      (56, 82), rot=0, pin_nets={"1": "CHRG_N", "2": "CHRG_LED"})
place(HDR, "PinHeader_1x03_P2.54mm_Vertical", "J13", "PWR-SEL", (78, 86),
      pin_nets={"1": "VPROT", "2": "+5V", "3": "VBOOST"})

# UART/backhaul column (RX, TX, GND, 5V) at x=40
place(HDR, "PinHeader_1x04_P2.54mm_Vertical", "J7", "UART", (40, 64),
      pin_nets={"1": "RX_D7", "2": "TX_D6", "3": "GND", "4": "+5V"})

# SPI/spare along bottom edge, rotated so pins run +x
# (3V3, GND, MOSI, MISO, SCK)
place(HDR, "PinHeader_1x05_P2.54mm_Vertical", "J8", "SPI", (15, 70),
      rot=90, pin_nets={"1": "+3V3", "2": "GND", "3": "MOSI_D10",
                        "4": "MISO_D9", "5": "SCK_D8"})

# battery/5V input (GND, 5V) — p2 sits on the 5V trunk
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      pin_nets={"1": "GND", "2": "+5V"})
# emit transducer terminal (EMIT_SW, 3V3)
place(HDR, "PinHeader_1x02_P2.54mm_Vertical", "J10", "EMIT-40k", (64, 68),
      pin_nets={"1": "EMIT_SW", "2": "+3V3"})

# emit driver passives
place("Resistor_SMD.pretty", "R_0805_2012Metric", "R1", "100R", (42, 52),
      pin_nets={"1": "D3_EMIT", "2": "EMIT_GATE"})
place("Capacitor_SMD.pretty", "C_0805_2012Metric", "C1", "100nF", (63, 28),
      pin_nets={"1": "+3V3", "2": "GND"})
place("Package_TO_SOT_SMD.pretty", "SOT-23", "Q1", "2N7002", (50, 52),
      pin_nets={"1": "EMIT_GATE", "2": "GND", "3": "EMIT_SW"})
# flyback diode, rotated so cathode faces right (toward 3V3)
place("Diode_SMD.pretty", "D_SOD-123", "D1", "1N4148W", (56, 52), rot=180,
      pin_nets={"1": "+3V3", "2": "EMIT_SW"})

# --- production: protected 5V input + signal TVS + power LED + fiducials
TB = "TerminalBlock_Phoenix.pretty"
place(TB, "TerminalBlock_Phoenix_MKDS-1,5-2_1x02_P5.00mm_Horizontal",
      "J11", "5V-SCREW", (80, 74.5), pin_nets={"1": "VIN", "2": "GND"})
place("Fuse.pretty", "Fuse_1206_3216Metric", "F1", "0.75A", (74, 74.5),
      pin_nets={"1": "VPROT", "2": "VIN"})
# rail TVS: rot=180 puts cathode (pad1) at +2.0 -> VPROT side
place("Diode_SMD.pretty", "D_SMA", "D3", "SMAJ5.0A", (68, 76), rot=180,
      pin_nets={"1": "VPROT", "2": "GND"})
# series Schottky (reverse-polarity): pad1 cathode -> +5V, pad2 anode <- VPROT
place("Diode_SMD.pretty", "D_SMA", "D2", "SS14", (59, 74.5),
      pin_nets={"1": "+5V", "2": "VPROT"})
# signal TVS on the exposed head inputs (cathode pad1 -> SIG, anode -> GND)
for ref, y, snet, gndy in [("D4", 22.5, "D0_PIR", 25.08),
                           ("D5", 32.5, "D1_HYDRO", 35.08),
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          rot=270, pin_nets={"1": snet, "2": "GND"})
# power LED: 3V3 -> R2 -> LED anode, LED cathode -> GND
place("Resistor_SMD.pretty", "R_0805_2012Metric", "R2", "1k", (71.5, 20),
      pin_nets={"1": "+3V3", "2": "LEDPWR"})
place("LED_SMD.pretty", "LED_0805_2012Metric", "LED1", "PWR-GRN",
      (76, 20), rot=180, pin_nets={"1": "GND", "2": "LEDPWR"})
# fiducials for the PCBA line (pad has no pin number -> netless marker)
for i, pos in enumerate([(10, 10), (88, 8.5), (10, 66)], start=1):
    place("Fiducial.pretty", "Fiducial_1mm_Mask3mm", "FID%d" % i,
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via((76.938, 22.5), "GND")
seg([(76.94, 22.5), (76.94, 24), (60.5, 24)], B, TRACK, "GND")

# --- E22: ANT pad -> SMA edge-mount centre pin on the right edge;
#     GND pads stitched to the pour
seg([(83.7, 17.75), (88, 17.75), (88, 16), (93.5, 16),
     (93.5, 18)], F, TRACK, "ANT")
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

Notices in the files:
tools/pcb/gen_node.py:
SPDX-License-Identifier: AGPL-3.0-or-later
hardware/pcb/ecocell-carrier.kicad_pcb:
EcoCell carrier v1 - living-resources AGPL
hardware/pcb/ecocell-node.kicad_pcb:
EcoCell One v1 - living-resources AGPL
